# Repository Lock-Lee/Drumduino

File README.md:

# DrumDuino

**English** · [ภาษาไทย](README.th.md)

An electronic drum app for macOS and Windows that works with an Arduino and piezo sensors.
Hit a pad and hear a real drum sample, practice along with the score and the original song, and record clips for social media, all in one app.
The app speaks Thai and English (switch with **ไทย | EN** in the top right).

## Features

**Drum sounds**
- 6 kits to choose from: Studio Maple, Black Pearl, Red Zeppelin, Arena Metal, Salamander Garage (real acoustic drums with several velocity layers) and Synth Kit
- Duplicate a kit into "My kit" and change its sounds; 3-band EQ (low / mid / high) per piece
- **Use your own samples, several per piece**: .wav .mp3 .ogg .flac .aiff (drag and drop), played by velocity layer · round robin · random
- Volume, pitch, sensor sensitivity and scan / mask time per piece, sent to the board automatically
- **Dual-zone pads**: head piezo + rim piezo with separate rim sounds (rimshot, ride bell, tom rim)
- **Hi-hat pedal**: closed / half-open / open by pedal depth, pedal "chick", open hi-hat chokes when the pedal closes, MIDI CC4 supported

**Practice**
- Standard 5-line drum notation with a moving cursor; click any bar to start from there
- **App plays** and **I play (scored)** modes (shows how many ms early / late, with a score) · metronome · count-in · BPM control · loop a range of bars · change kit right on the page
- **Lanes tab**: notes scroll toward you in colored lanes per piece, every note marked with its hand L / R or foot RF / LF, with a neon kit
- **3D drum kit**: the sticks move like real hands, lifting ahead of the next note and striking exactly on the beat. Hands alternate like a drummer (rolls and fills go R L R L), cymbals wobble, the kick beater swings. Click a drum to hit it, drag to orbit the view
- **Backing track + Auto Sync**: add the real song and the app works out which second bar 1 starts at and the song's actual BPM, then keeps the song in time with the score all the way through. Slowing down keeps the pitch
- Built-in grooves (rock, pop, funk, disco, shuffle, swing, bossa, 6/8, fills, practice songs with sections) and MIDI / MusicXML import (exports from MuseScore work)

**Recording**
- **Recording mode** in portrait or 16:9 landscape hides all menus, leaving only the notes and the 3D kit
- A script sets up OBS completely for Reels (9:16) and YouTube (16:9): the app window fills the picture, with the Mac's sound

**Hardware**
- Input over USB Serial (any board) or USB MIDI (Leonardo / Pro Micro); Arduino Mega gives 16 channels (A0–A15)
- PCB design for the Mega 2560 PRO with 16 × 6.35 mm jacks, plus a 3D-printed case
- No Arduino? Test with the keyboard, or **use an iPhone / iPad as wireless pads**: turn on *Play from iPhone / iPad* in the Hardware tab and scan the QR code. Taps play through the Mac over Wi-Fi (realistic kit with double kick, multi-touch, harder in the middle of a pad, hold-to-open hi-hat). Press Play and a ring in the drum's colour closes in on the pad you need to hit next, with the hand (L / R / RF / LF)
- Everything saves automatically; sample files stay on your computer

## Examples

### Example 1: practice along with a real song using Auto Sync

1. Open the **Practice** tab and pick a song from the list on the left
2. In the **Backing track** strip, press **♪ Choose audio file…** and pick the song's mp3 / m4a / wav
3. Wait 3–5 seconds: the app syncs it by itself and shows ✓ Synced
4. Press **Space** to play. The song plays its intro first, and the notes start moving exactly at bar 1

This screenshot uses a test track rendered from the "เพลงฝึก: Arena Metalcore" score (written at 144 BPM),
with a 4-second intro before the drums and played slightly faster than the score, at 146 BPM.
The app found bar 1 at **0:04.0** and the tempo at **145.9 BPM**, and set the playback speed to match.

| To do this | Do this |
|---|---|
| Practice slower | Move the speed slider: the song slows down too, without changing pitch |
| Drill one section | Enter the start–end bars and tick **Loop**: the song jumps along with it |
| Hear only the song and play yourself | Choose **I play (scored)**: the app's drums go quiet and you get a score |
| Song still slightly off | Press **Adjust** and use −/+ (song ahead of the drums → −, song behind → +) |

Auto Sync works best on studio recordings at a steady tempo where the score matches the recording's version.
If the song speeds up or slows down partway, or the score has a different number of bars than the song, it drifts from that point on.

### Example 2: import a score from MuseScore

1. In MuseScore, open the drum score and choose *File → Export → MIDI* (or MusicXML)
2. In the app press **Import MIDI / MusicXML** and pick the file

For many songs, press **Open folder** and put the files in the `my-scores` folder; the app loads them every time it starts.

```
my-scores/
├── song 1.mid
├── song 2.musicxml
└── ...
```

During development this folder is `./my-scores` in the project (gitignored, so personal scores never reach git).
In the installed app it lives in the app's data folder.
Section names (Markers) in a MIDI file appear as section labels on the score, and you can jump to them.

### Example 3: add your own snare with 6 velocity layers

1. In the **Kit** tab press **Duplicate** to make your own kit
2. Click **Snare** and drag `snare_01.wav` … `snare_06.wav` (soft to loud) into the box on the right
3. Set **Multiple files → By velocity**: the app splits the velocity range for you (1–21, 22–42, … 107–127)
4. In **Settings**, adjust volume, pitch and the low/mid/high EQ

### Example 4: record a drum clip with OBS

```bash
# Close OBS first, then run once (macOS)
python3 obs/setup_obs.py
open -a OBS --args --collection "DrumDuino Reels" --profile "DrumDuino Reels"
```

The script creates two scene collections + profiles (60 fps, clips saved to `~/Movies/DrumDuino`):

| Collection / profile | Size | Use with recording mode | For |
|---|---|---|---|
| DrumDuino Reels | 1080×1920 (9:16) | Portrait | Reels, TikTok, Shorts |
| DrumDuino | 1920×1080 (16:9) | Landscape (full) | YouTube |

Each has one scene, **แอปเต็มจอ**: the notes and 3D kit fill the whole picture, no camera. Switch between them in OBS under *Scene Collection* and *Profile*.

In the app's Practice or Lanes tab, press **● Record → Portrait** or **Landscape (full)**. The window shrinks and moves to exactly where OBS captures it (don't drag the window).
Space plays / stops, Esc leaves recording mode.
Sound is the Mac's own output (drums + backing track), so turn on Do Not Disturb while recording to keep notification sounds out.

### Example 5: try it without an Arduino

Open the app and use the keyboard as drum pads.

| Key | Drum | | Key | Drum |
|---|---|---|---|---|
| Q | Crash | | A | Hi-hat |
| W | Tom 1 | | S | Snare |
| E | Tom 2 | | D | Kick |
| R | Ride | | F | Floor Tom |

Hold Shift = soft hit · Option/Alt = rim · hold X = open hi-hat · Z = hi-hat pedal

## Hardware

| Board | Channels | Connection |
|---|---|---|
| Arduino Nano | 8 (A0–A7) | USB Serial |
| Arduino Uno | 6 (A0–A5) | USB Serial |
| Arduino Mega | 16 (A0–A15) | USB Serial |
| Leonardo / Pro Micro | 8 | USB Serial + USB MIDI |

Wiring per channel: piezo (+) → analog pin, piezo (−) → GND, a 1 MΩ resistor across the analog pin and GND.
Recommended: a 5.1 V Zener diode across them for overvoltage protection.

Firmware: open `firmware/DrumDuino/DrumDuino.ino` in the Arduino IDE → pick the board/port → Upload
(Leonardo / Pro Micro need the `MIDIUSB` library installed first).

Default pins: A0 Crash · A1 Hi-hat · A2 Snare · A3 Kick · A4 Tom 1 · A5 Tom 2 · A6 Floor Tom · A7 Ride

### PCB and case (Mega 2560 PRO)

- **140 × 120 mm PCB:** 16 × 6.35 mm jacks, each channel protected (1 MΩ + 5.1 V Zener), a hi-hat pedal channel and a DC power jack.
  KiCad files, Gerbers for JLCPCB and the BOM are in [`hardware/drumduino-carrier/`](hardware/drumduino-carrier/README.md)
- **3D-printed case:** separate base and lid held by 4 × M3 × 25 mm screws. STL files are in [`hardware/enclosure/`](hardware/enclosure/README.md)

Example pad hookup: piezo cable → mono 1/4" plug → jack A2 on the case → shows up as Snare in the app right away.

## Development

Requires [Node.js](https://nodejs.org) 20 or newer.

```bash
npm install
npm run dev        # run the app with hot reload
```

## Building installers

```bash
npm run dist:mac   # must run on a Mac     → release/DrumDuino-x.y.z-arm64.dmg and -x64.dmg
npm run dist:win   # must run on Windows   → release/DrumDuino Setup x.y.z.exe
```

### Let GitHub build both (no Mac/Windows machine needed)

The workflow is already in `.github/workflows/build.yml`.

1. Push this project to GitHub
2. Tag a version and push it: `git tag v0.1.0 && git push --tags`
3. After about 10 minutes the `.dmg` and `.exe` files appear on the **Releases** page
   (or press Run workflow in the Actions tab and download from Artifacts)

### Installing notes

The installers aren't signed with an Apple/Microsoft certificate yet, so the first launch shows a warning:

- **macOS**: drag the app to Applications, then right-click it → Open → Open.
  If it says the app is "damaged", run in Terminal: `xattr -cr /Applications/DrumDuino.app`
- **Windows**: if SmartScreen appears, click *More info* → *Run anyway*

To distribute to the public, get an Apple Developer ID ($99/year) and a Windows code-signing certificate and configure them in electron-builder.

## Serial protocol (115200 baud)

Real messages after plugging in the board, then hitting the snare, the snare rim, and pressing the hi-hat pedal halfway:

```
← I DRUMDUINO 1.2 16        board introduces itself: firmware 1.2, 16 channels
→ T 2 40                    app sets the threshold of A2 (Snare) = 40
← H 2 96                    snare head hit, velocity 96
← H 2 110 R                 snare rim hit, velocity 110
← C 15 512                  hi-hat pedal (A15) mid-travel ≈ half-open (depends on pedal calibration)
```

All messages:

```
board → app   I DRUMDUINO <version> <channels>
              H <channel> <velocity 1–127> [R]     R = rim
              C <channel> <raw 0–1023>             hi-hat pedal position
app → board   E <channel> <0|1>                    enable / disable a pin
              T <channel> <threshold 0–1023>
              S <channel> <scan ms>
              M <channel> <mask ms>
              P <head channel> <rim channel|-1>    pair a rim pin with a head pin
              X <head channel> <ratio %>           rim hit when rim ≥ head × ratio/100
              K <channel> <0|1>                    1 = this pin is a pedal (continuous sensor)
              ?
```

## Project layout

```
electron/        main process (window, Serial/MIDI permissions, port picker, recording mode)
src/audio/       audio engine, built-in kits, backing track + Auto Sync (backing.ts, align.ts)
src/input/       Serial, MIDI, keyboard
src/score/       notation (VexFlow), score player, MIDI/MusicXML import, 3D kit, lane view, sticking
src/pages/       Kit / Practice / Lanes / Sounds / Hardware pages
src/i18n/        Thai / English UI text
firmware/        Arduino code
hardware/        PCB (KiCad) and 3D-printed case
obs/             OBS setup script for recording
docs/images/     README images
```

## Sound credits

- **Studio Maple**: [Virtuosity Drums](https://versilian-studios.com/virtuosity-drums/) by Versilian Studios, CC0 license.
  Mixed from the kick + snare + overhead mics with a selection of velocity layers (`public/samples/LICENSE-VirtuosityDrums-CC0.txt`)
- **Black Pearl / Red Zeppelin**: [AVL Drumkits](https://github.com/studiorack/avl-drumkits) by Glen MacArthur ([bandshed.net](http://www.bandshed.net/avldrumkits/)),
  [CC BY-SA 3.0](https://creativecommons.org/licenses/by-sa/3.0/). Converted to stereo OGG, silent tails trimmed, panned as in the original SFZ files.
  These samples (including the modified ones) are redistributed under the same CC BY-SA 3.0 (`public/samples/avl/LICENSE-AVL-Drumkits-CC-BY-SA-3.0.txt`)
- **Salamander Garage**: [Salamander Drumkit](https://github.com/studiorack/salamander-drumkit) by Alexander Holm (Rytmenpinne),
  [CC BY-SA 3.0](https://creativecommons.org/licenses/by-sa/3.0/). 3–8 velocity layers chosen per piece, converted to OGG, shortened and level-matched by velocity.
  The modified files are redistributed under the same CC BY-SA 3.0 (`public/samples/sal/LICENSE-Salamander-Drumkit-CC-BY-SA-3.0.txt`)
- **Synth Kit**: generated in the app

## License

Copyright © 2026 Thirawut Khanpan. **All rights reserved.** The code, firmware, designs, PCB and enclosure files are proprietary: copying, modifying, redistributing or using them commercially is not allowed without written permission. The drum samples listed above keep their own licenses (CC0 / CC BY-SA 3.0). See [LICENSE](LICENSE).

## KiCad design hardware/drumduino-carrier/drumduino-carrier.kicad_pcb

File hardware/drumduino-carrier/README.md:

# DrumDuino Carrier v2.0 (บอร์ดฐานสำหรับ Mega 2560 PRO)

แผ่น PCB 2 ชั้น ขนาด 140 × 120 มม. ใช้เป็นบอร์ดฐานของ **Mega 2560 PRO (Embed)** ของ RobotDyn หรือรุ่นที่ขาเหมือนกัน
บอร์ด Mega PRO เสียบลงบนเฮดเดอร์ตัวเมียที่บัดกรีไว้บนแผ่นนี้

- **แจ็ค 6.35 มม. 16 ช่องบนแผ่น:** ขอบบน 8 ช่อง ขอบล่าง 8 ช่อง หัวแจ็คยื่นออกนอกขอบแผ่นเพื่อลอดรูของกล่อง
- **วงจรป้องกันทุกช่อง:** ตัวต้านทาน 1 MΩ และซีเนอร์ 5.1V ต่อลง GND
- **ช่อง A15 สำหรับแป้นไฮแฮท:** TIP = ขากลางของ pot, RING = VCC, SLEEVE = GND
- **ช่องไฟ DC 5.5 × 2.1 มม.:** ไฟผ่านไดโอด 1N5819 กันต่อขั้วกลับ แล้วเข้าขา VIN ใช้อแดปเตอร์ 9V แบบขั้วบวกอยู่ตรงกลาง
  ถ้าเสียบแค่ USB บอร์ดก็ทำงานได้

เปิดโปรเจกต์ด้วย KiCad 7 ขึ้นไป โดยเปิดไฟล์ `drumduino-carrier.kicad_pro`
โมเดล 3D ทุกชิ้นอยู่ในโฟลเดอร์ `3dmodels` ของโปรเจกต์ กด Alt+3 ใน PCB Editor เพื่อดูภาพ 3D

## ไฟล์สำหรับสั่งทำแผ่น
- `fab/drumduino-carrier-v2-gerbers-JLCPCB.zip` อัปโหลดไฟล์นี้ที่ jlcpcb.com ได้เลย ใช้ค่ามาตรฐาน: 2 layers, 1.6 mm, HASL
- `fab/drumduino-carrier-schematic.pdf` วงจร
- `fab/drumduino-carrier-v2-3d.png` ภาพ 3D

## รายการอุปกรณ์ (BOM)
| Ref | จำนวน | อุปกรณ์ | หมายเหตุ |
|---|---|---|---|
| U1 | 1 | Mega 2560 PRO (Embed) CH340 | บัดกรีขาตัวผู้ใต้บอร์ด |
| – | 1 | เฮดเดอร์ตัวเมีย 2×16 ขา 2.54 มม. (หรือ 1×16 จำนวน 2 แถว) | สูง 8.5 มม. |
| – | 1 | เฮดเดอร์ตัวเมีย 2×3 ขา 2.54 มม. | ตรง VIN / GND / VCC |
| J1–J16 | 16 | แจ็คสเตริโอ 6.35 มม. ลงแผ่น **Rean (Neutrik) NRJ6HF** หรือ NRJ6HF-1 | ราว 35 บาท/ตัว มีขายที่ Thomann, Mouser, Digi-Key, TME |
| J17 | 1 | แจ็คไฟ DC 5.5 × 2.1 มม. ลงแผ่น (DC-005) | ขาตรงกับลาย BarrelJack_Horizontal ของ KiCad |
| D17 | 1 | 1N5819 (Schottky 1A) | กันต่อขั้วกลับ แถบหันเข้าหา VIN |
| R1–R16 | 16 | ตัวต้านทาน 1 MΩ 1/4W | ใส่แบบตั้ง |
| D1–D16 | 16 | ซีเนอร์ 1N4733A (5.1V 1W) | ใส่แบบตั้ง **ขาด้านที่มีแถบ (K) ลงแผ่นสี่เหลี่ยม** |
| H1–H4 | 4 | เสารอง M3 | |

## การต่อสาย
- **แป้นทั่วไป:** ใช้สายกีตาร์โมโน 6.35 มม. ตัวผู้–ตัวผู้ ต่อจากแจ็คของ piezo มาที่แจ็คบนแผ่น
  RING ของแจ็คบนแผ่นไม่ได้ต่อใช้งาน สายโมโนเสียบได้ปกติ
- **แป้นไฮแฮท:** ใช้สายสเตริโอ (TRS) และต่อ pot 10 kΩ ดังนี้: TIP = ขากลาง, RING = ขาข้างหนึ่ง, SLEEVE = ขาอีกข้าง
  **อย่าเสียบสายโมโนเข้าช่อง A15** เพราะสายโมโนจะต่อ RING (VCC) ลง GND
- **ถ้าจะตีขอบ:** ใช้ piezo แผ่นที่ 2 เสียบเข้าอีกช่องหนึ่ง เช่น A8 สำหรับขอบสแนร์ หรือ A9 สำหรับระฆังไรด์

## ช่องที่ตั้งไว้ (พิมพ์ไว้บนแผ่น)
| ขอบบน | | ขอบล่าง | |
|---|---|---|---|
| A0 | Crash | A1 | Hi-hat |
| A2 | Snare | A3 | Kick |
| A4 | Tom 1 | A5 | Tom 2 |
| A6 | Floor | A7 | Ride |
| A8 | ขอบสแนร์ | A9 | ระฆังไรด์ |
| A10, A12, A14 | ว่าง | A11, A13 | ว่าง |
| | | A15 | แป้นไฮแฮท |

ช่อง A0–A7 ตรงกับค่าเริ่มต้นของแอป DrumDuino อยู่แล้ว
ส่วนขอบสแนร์, ระฆังไรด์ และแป้นไฮแฮท ให้ไปตั้งในหน้า **ฮาร์ดแวร์** ของแอป

## ข้อควรระวัง
- พอร์ต USB ของบอร์ด Mega PRO อยู่ขอบซ้ายของแผ่น ให้เว้นช่องที่กล่องไว้เสียบสาย
- ก่อนสั่งทำแผ่น ให้เทียบขาของบอร์ด Mega PRO ที่ซื้อมาว่าตรงกับลายบนแผ่น:
  แถวบน A0, A2 … A14 / แถวล่าง A1, A3 … A15 และมุมซ้ายล่าง VIN, GND, VCC
- แผ่นใหญ่กว่า 100 × 100 มม. ค่าทำแผ่นที่ JLCPCB จะแพงกว่าราคาต่ำสุดเล็กน้อย
- โมเดล 3D ของบอร์ด Mega PRO และแจ็ค Rean เป็นรูปทรงคร่าว ๆ ที่ทำเอง ไว้ดูตำแหน่งและความสูงเท่านั้น
  ส่วนชิ้นอื่นเป็นโมเดลทางการของ KiCad 7

ไฟล์ทั้งหมดในโฟลเดอร์นี้สร้างจาก `../gen_carrier.py` ถ้าแก้ตำแหน่งหรือจำนวนช่อง ให้แก้สคริปต์แล้วรันใหม่

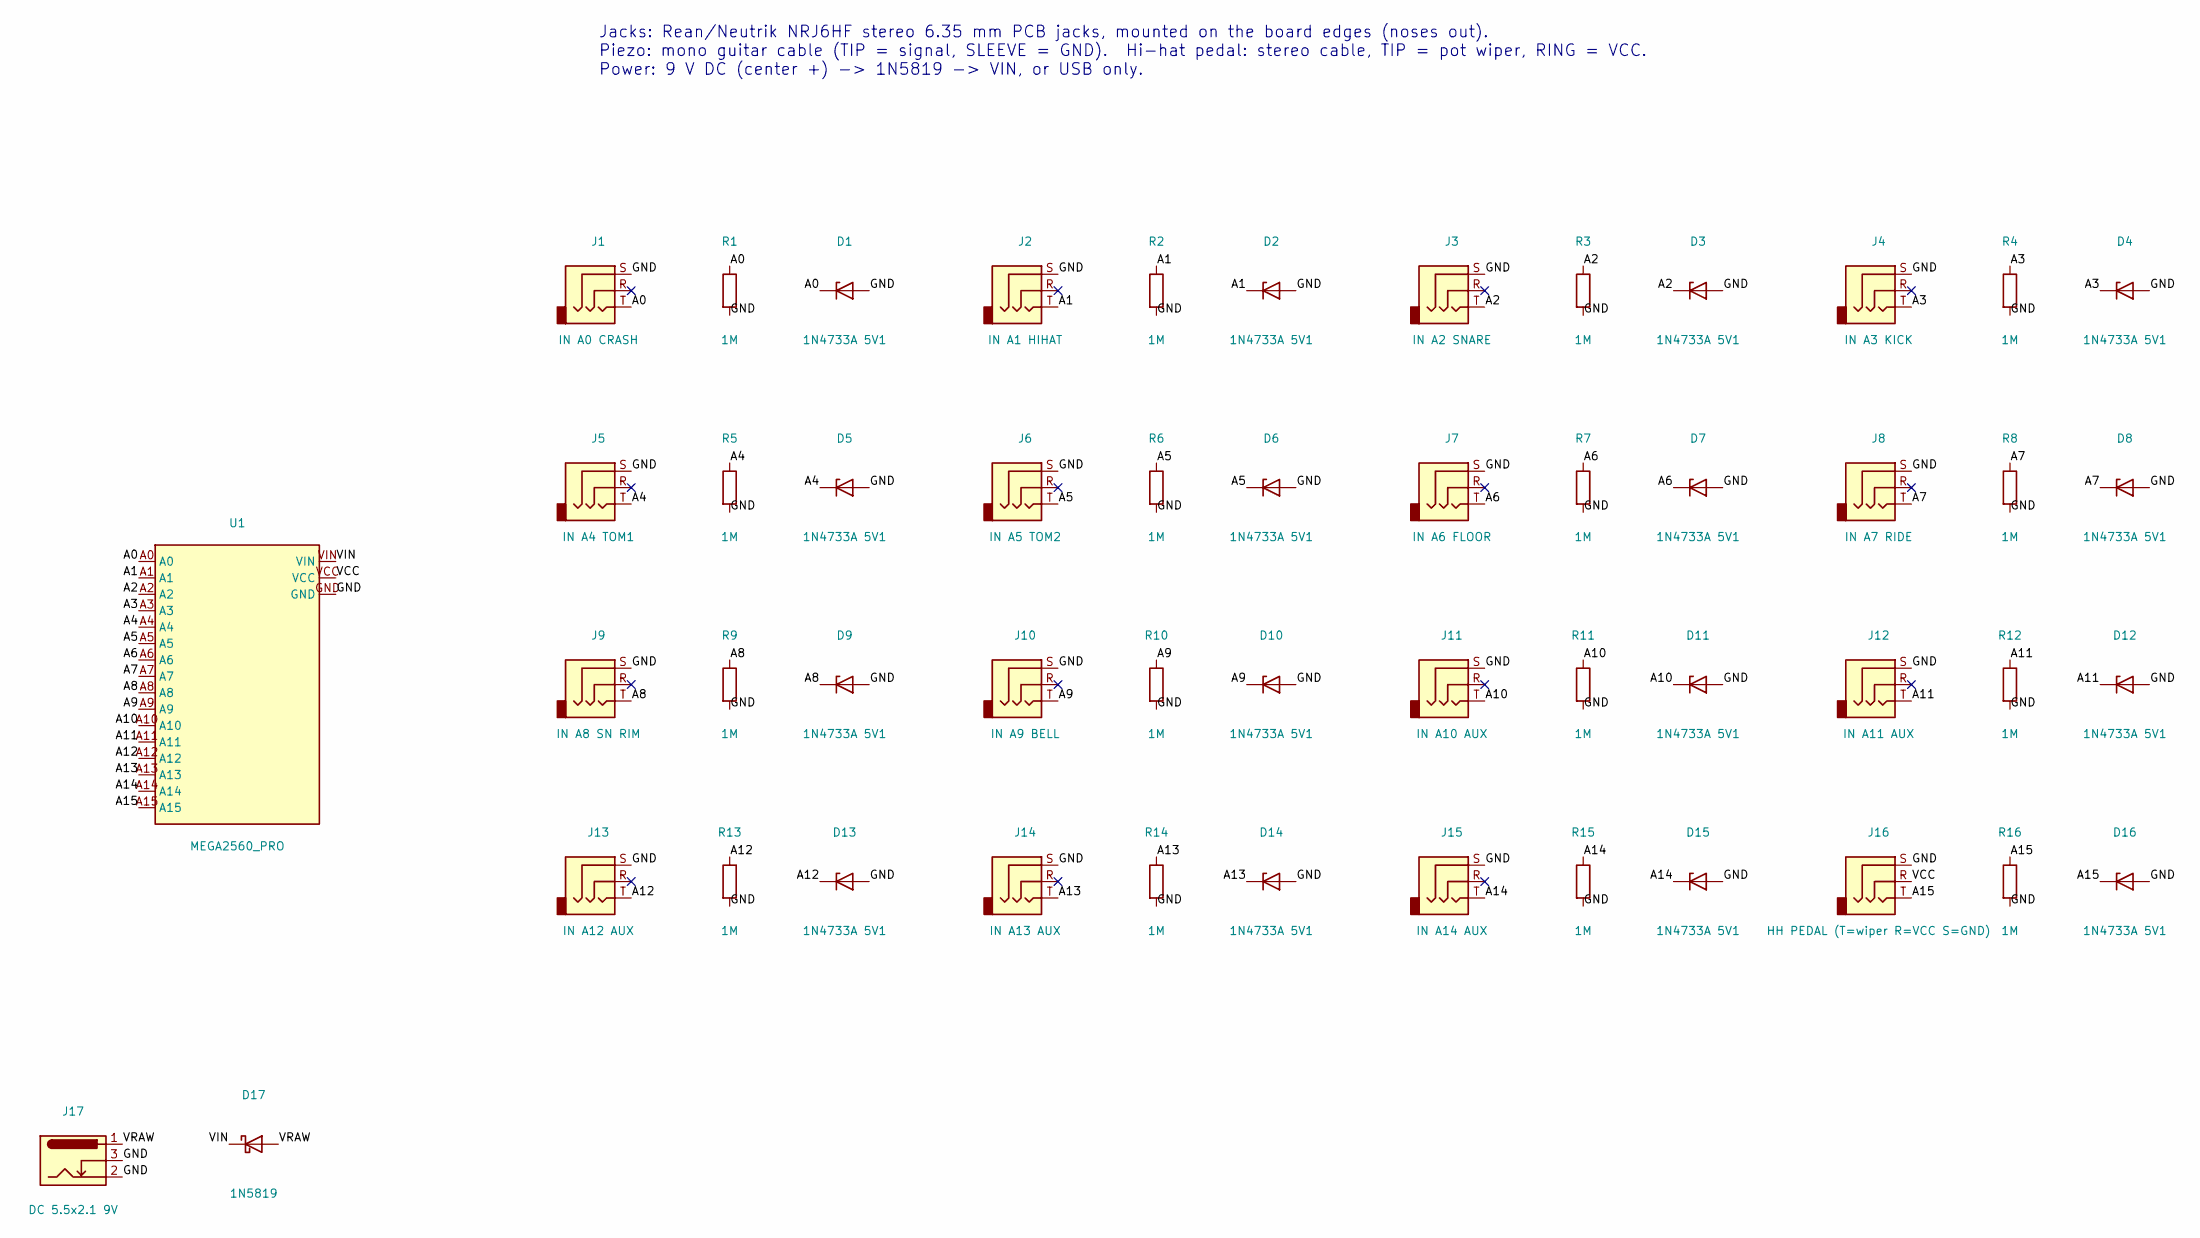
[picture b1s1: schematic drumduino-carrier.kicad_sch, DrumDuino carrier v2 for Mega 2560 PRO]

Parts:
D1, D2, D3, D4, D5, D6, D7, D8, D9, D10, D11, D12, D13, D14, D15, D16: 1N4733A 5V1; D_DO-41_SOD81_P2.54mm_Vertical_AnodeUp
D17: 1N5819; D_DO-41_SOD81_P10.16mm_Horizontal
J1: IN A0 CRASH; Jack_6.35mm_Neutrik_NRJ6HF_Horizontal
J2: IN A1 HIHAT; Jack_6.35mm_Neutrik_NRJ6HF_Horizontal
J3: IN A2 SNARE; Jack_6.35mm_Neutrik_NRJ6HF_Horizontal
J4: IN A3 KICK; Jack_6.35mm_Neutrik_NRJ6HF_Horizontal
J5: IN A4 TOM1; Jack_6.35mm_Neutrik_NRJ6HF_Horizontal
J6: IN A5 TOM2; Jack_6.35mm_Neutrik_NRJ6HF_Horizontal
J7: IN A6 FLOOR; Jack_6.35mm_Neutrik_NRJ6HF_Horizontal
J8: IN A7 RIDE; Jack_6.35mm_Neutrik_NRJ6HF_Horizontal
J9: IN A8 SN RIM; Jack_6.35mm_Neutrik_NRJ6HF_Horizontal
J10: IN A9 BELL; Jack_6.35mm_Neutrik_NRJ6HF_Horizontal
J11: IN A10 AUX; Jack_6.35mm_Neutrik_NRJ6HF_Horizontal
J12: IN A11 AUX; Jack_6.35mm_Neutrik_NRJ6HF_Horizontal
J13: IN A12 AUX; Jack_6.35mm_Neutrik_NRJ6HF_Horizontal
J14: IN A13 AUX; Jack_6.35mm_Neutrik_NRJ6HF_Horizontal
J15: IN A14 AUX; Jack_6.35mm_Neutrik_NRJ6HF_Horizontal
J16: HH PEDAL (T=wiper R=VCC S=GND); Jack_6.35mm_Neutrik_NRJ6HF_Horizontal
J17: DC 5.5x2.1 9V; BarrelJack_Horizontal
R1, R2, R3, R4, R5, R6, R7, R8, R9, R10, R11, R12, R13, R14, R15, R16: 1M; R_Axial_DIN0207_L6.3mm_D2.5mm_P2.54mm_Vertical
U1: MEGA2560_PRO; MEGA2560_PRO_Socket

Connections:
A0: D1.1 (K), J1.T, R1.1, U1.A0
A1: D2.1 (K), J2.T, R2.1, U1.A1
A2: D3.1 (K), J3.T, R3.1, U1.A2
A3: D4.1 (K), J4.T, R4.1, U1.A3
A4: D5.1 (K), J5.T, R5.1, U1.A4
A5: D6.1 (K), J6.T, R6.1, U1.A5
A6: D7.1 (K), J7.T, R7.1, U1.A6
A7: D8.1 (K), J8.T, R8.1, U1.A7
A8: D9.1 (K), J9.T, R9.1, U1.A8
A9: D10.1 (K), J10.T, R10.1, U1.A9
A10: D11.1 (K), J11.T, R11.1, U1.A10
A11: D12.1 (K), J12.T, R12.1, U1.A11
A12: D13.1 (K), J13.T, R13.1, U1.A12
A13: D14.1 (K), J14.T, R14.1, U1.A13
A14: D15.1 (K), J15.T, R15.1, U1.A14
A15: D16.1 (K), J16.T, R16.1, U1.A15
GND: D1.2 (A), D2.2 (A), D3.2 (A), D4.2 (A), D5.2 (A), D6.2 (A), D7.2 (A), D8.2 (A), D9.2 (A), D10.2 (A), D11.2 (A), D12.2 (A), D13.2 (A), D14.2 (A), D15.2 (A), D16.2 (A), J1.S, J2.S, J3.S, J4.S, J5.S, J6.S, J7.S, J8.S, J9.S, J10.S, J11.S, J12.S, J13.S, J14.S, J15.S, J16.S, J17.2, J17.3, R1.2, R2.2, R3.2, R4.2, R5.2, R6.2, R7.2, R8.2, R9.2, R10.2, R11.2, R12.2, R13.2, R14.2, R15.2, R16.2, U1.GND
VCC: J16.R, U1.VCC
VIN: D17.1 (K), U1.VIN
VRAW: D17.2 (A), J17.1

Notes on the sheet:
Jacks: Rean/Neutrik NRJ6HF stereo 6.35 mm PCB jacks, mounted on the board edges (noses out). Piezo: mono guitar cable (TIP = signal, SLEEVE = GND). Hi-hat pedal: stereo cable, TIP = pot wiper, RING = VCC. Power: 9 V DC (center +) -> 1N5819 -> VIN, or USB only.

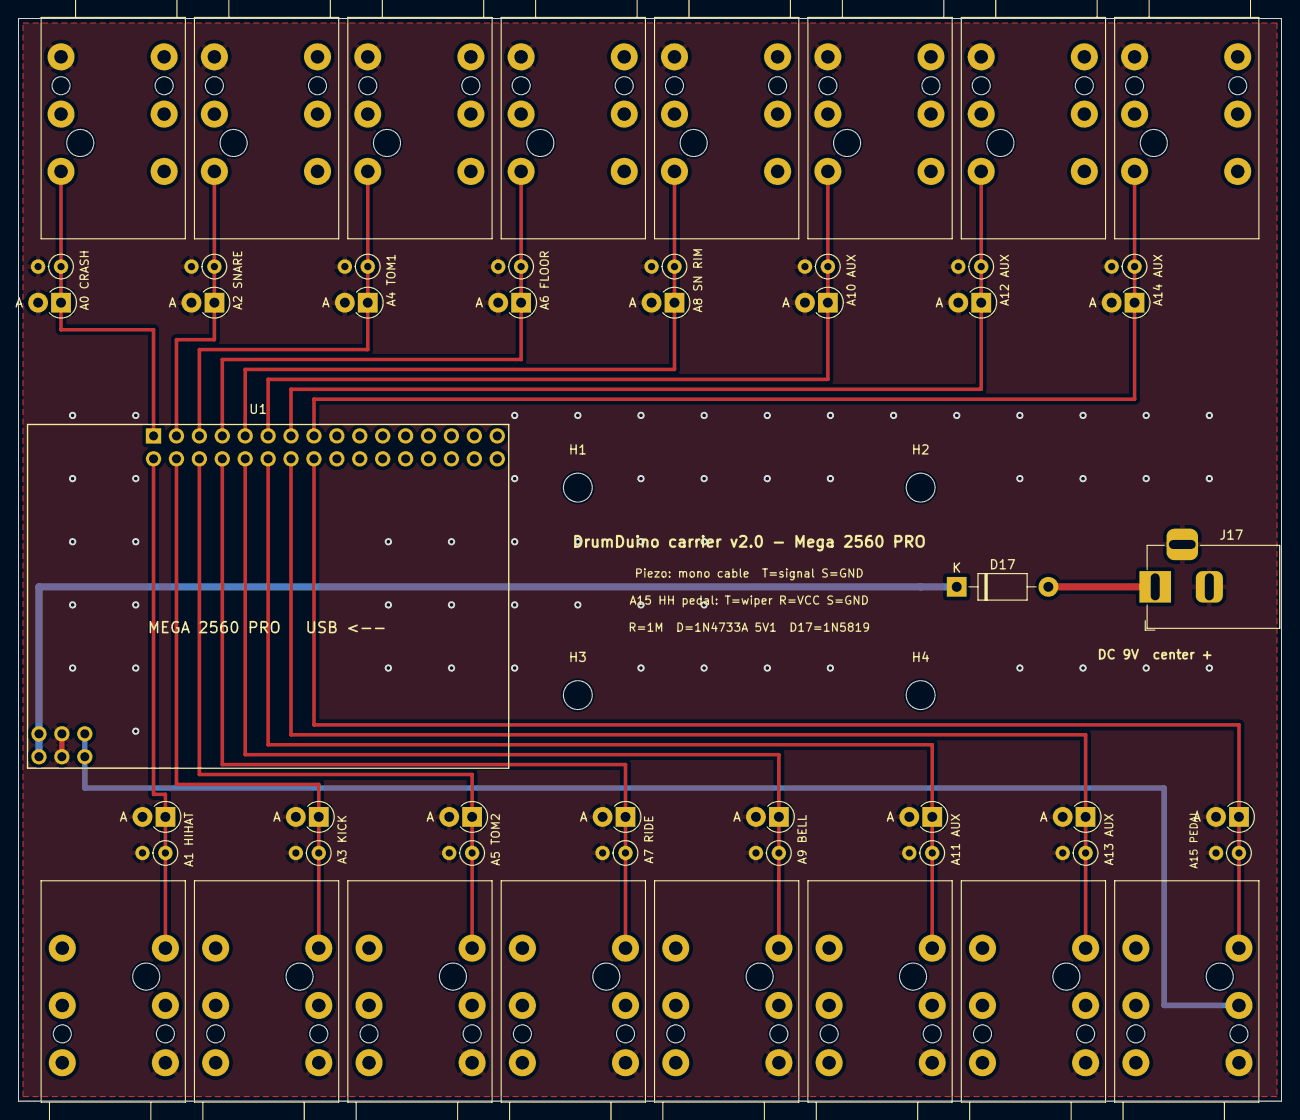
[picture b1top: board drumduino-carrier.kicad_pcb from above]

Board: 2 copper layers, 140.0 x 120.0 mm, 55 parts (0 on the bottom side), 20 nets.

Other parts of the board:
H1, H2, H3, H4: MountingHole_3.2mm_M3
